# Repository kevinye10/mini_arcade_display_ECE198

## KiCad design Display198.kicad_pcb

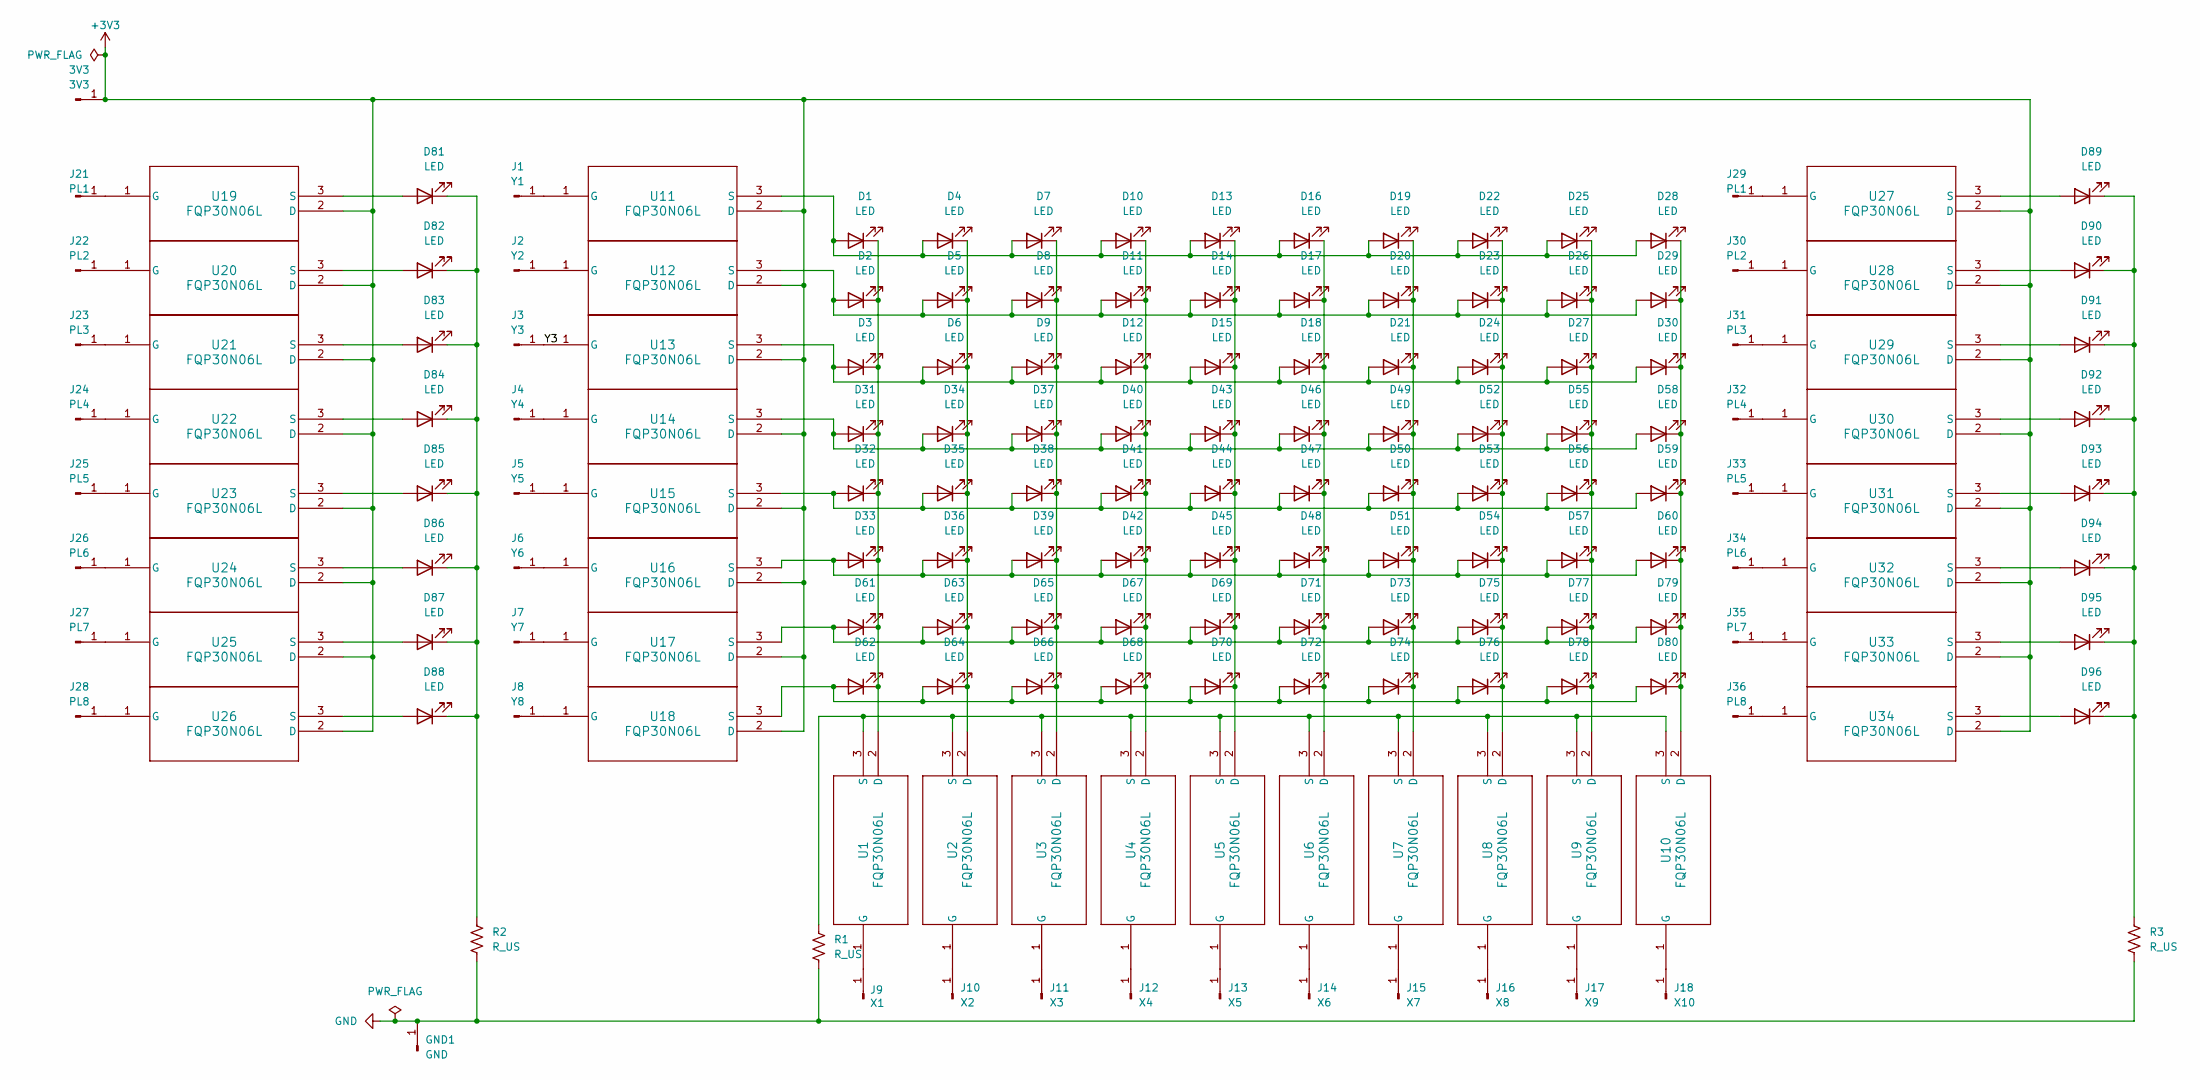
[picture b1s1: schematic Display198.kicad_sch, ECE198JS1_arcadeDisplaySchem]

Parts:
3V3: 3V3; Pin_D1.0mm_L10.0mm
D1, D2, D3, D4, D5, D6, D7, D8, D9, D10, D11, D12, D13, D14, D15, D16, D17, D18, D19, D20, D21, D22, D23, D24, D25, D26, D27, D28, D29, D30, D31, D32, D33, D34, D35, D36, D37, D38, D39, D40, D41, D42, D43, D44, D45, D46, D47, D48, D49, D50, D51, D52, D53, D54, D55, D56, D57, D58, D59, D60, D61, D62, D63, D64, D65, D66, D67, D68, D69, D70, D71, D72, D73, D74, D75, D76, D77, D78, D79, D80, D81, D82, D83, D84, D85, D86, D87, D88, D89, D90, D91, D92, D93, D94, D95, D96: LED; D_5W_P5.08mm_Vertical_AnodeUp
GND1: GND; Pin_D1.0mm_L10.0mm
J1: Y1; Pin_D1.0mm_L10.0mm
J2: Y2; Pin_D1.0mm_L10.0mm
J3: Y3; Pin_D1.0mm_L10.0mm
J4: Y4; Pin_D1.0mm_L10.0mm
J5: Y5; Pin_D1.0mm_L10.0mm
J6: Y6; Pin_D1.0mm_L10.0mm
J7: Y7; Pin_D1.0mm_L10.0mm
J8: Y8; Pin_D1.0mm_L10.0mm
J9: X1; Pin_D1.0mm_L10.0mm
J10: X2; Pin_D1.0mm_L10.0mm
J11: X3; Pin_D1.0mm_L10.0mm
J12: X4; Pin_D1.0mm_L10.0mm
J13: X5; Pin_D1.0mm_L10.0mm
J14: X6; Pin_D1.0mm_L10.0mm
J15: X7; Pin_D1.0mm_L10.0mm
J16: X8; Pin_D1.0mm_L10.0mm
J17: X9; Pin_D1.0mm_L10.0mm
J18: X10; Pin_D1.0mm_L10.0mm
J21, J29: PL1; Pin_D1.0mm_L10.0mm
J22, J30: PL2; Pin_D1.0mm_L10.0mm
J23, J31: PL3; Pin_D1.0mm_L10.0mm
J24, J32: PL4; Pin_D1.0mm_L10.0mm
J25, J33: PL5; Pin_D1.0mm_L10.0mm
J26, J34: PL6; Pin_D1.0mm_L10.0mm
J27, J35: PL7; Pin_D1.0mm_L10.0mm
J28, J36: PL8; Pin_D1.0mm_L10.0mm
R1, R2, R3: R_US; R_Axial_DIN0411_L9.9mm_D3.6mm_P7.62mm_Vertical
U1, U2, U3, U4, U5, U6, U7, U8, U9, U10, U11, U12, U13, U14, U15, U16, U17, U18, U19, U20, U21, U22, U23, U24, U25, U26, U27, U28, U29, U30, U31, U32, U33, U34: FQP30N06L; TO220-3_ONS

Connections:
+3V3: 3V3.1, U11.2 (D), U12.2 (D), U13.2 (D), U14.2 (D), U15.2 (D), U16.2 (D), U17.2 (D), U18.2 (D), U19.2 (D), U20.2 (D), U21.2 (D), U22.2 (D), U23.2 (D), U24.2 (D), U25.2 (D), U26.2 (D), U27.2 (D), U28.2 (D), U29.2 (D), U30.2 (D), U31.2 (D), U32.2 (D), U33.2 (D), U34.2 (D)
/Y3: J3.1, U13.1 (G)
GND: GND1.1, R1.1, R2.1, R3.1
unnamed: D1.2 (A), D4.2 (A), D7.2 (A), D10.2 (A), D13.2 (A), D16.2 (A), D19.2 (A), D22.2 (A), D25.2 (A), D28.2 (A), U11.3 (S)
unnamed: D1.1 (K), D2.1 (K), D3.1 (K), D31.1 (K), D32.1 (K), D33.1 (K), D61.1 (K), D62.1 (K), U1.2 (D)
unnamed: D10.1 (K), D11.1 (K), D12.1 (K), D40.1 (K), D41.1 (K), D42.1 (K), D67.1 (K), D68.1 (K), U4.2 (D)
unnamed: D2.2 (A), D5.2 (A), D8.2 (A), D11.2 (A), D14.2 (A), D17.2 (A), D20.2 (A), D23.2 (A), D26.2 (A), D29.2 (A), U12.3 (S)
unnamed: D3.2 (A), D6.2 (A), D9.2 (A), D12.2 (A), D15.2 (A), D18.2 (A), D21.2 (A), D24.2 (A), D27.2 (A), D30.2 (A), U13.3 (S)
unnamed: D13.1 (K), D14.1 (K), D15.1 (K), D43.1 (K), D44.1 (K), D45.1 (K), D69.1 (K), D70.1 (K), U5.2 (D)
unnamed: D16.1 (K), D17.1 (K), D18.1 (K), D46.1 (K), D47.1 (K), D48.1 (K), D71.1 (K), D72.1 (K), U6.2 (D)
unnamed: D19.1 (K), D20.1 (K), D21.1 (K), D49.1 (K), D50.1 (K), D51.1 (K), D73.1 (K), D74.1 (K), U7.2 (D)
unnamed: D22.1 (K), D23.1 (K), D24.1 (K), D52.1 (K), D53.1 (K), D54.1 (K), D75.1 (K), D76.1 (K), U8.2 (D)
unnamed: D25.1 (K), D26.1 (K), D27.1 (K), D55.1 (K), D56.1 (K), D57.1 (K), D77.1 (K), D78.1 (K), U9.2 (D)
unnamed: D28.1 (K), D29.1 (K), D30.1 (K), D58.1 (K), D59.1 (K), D60.1 (K), D79.1 (K), D80.1 (K), U10.2 (D)
unnamed: D31.2 (A), D34.2 (A), D37.2 (A), D40.2 (A), D43.2 (A), D46.2 (A), D49.2 (A), D52.2 (A), D55.2 (A), D58.2 (A), U14.3 (S)
unnamed: D32.2 (A), D35.2 (A), D38.2 (A), D41.2 (A), D44.2 (A), D47.2 (A), D50.2 (A), D53.2 (A), D56.2 (A), D59.2 (A), U15.3 (S)
unnamed: D33.2 (A), D36.2 (A), D39.2 (A), D42.2 (A), D45.2 (A), D48.2 (A), D51.2 (A), D54.2 (A), D57.2 (A), D60.2 (A), U16.3 (S)
unnamed: D4.1 (K), D5.1 (K), D6.1 (K), D34.1 (K), D35.1 (K), D36.1 (K), D63.1 (K), D64.1 (K), U2.2 (D)
unnamed: D7.1 (K), D8.1 (K), D9.1 (K), D37.1 (K), D38.1 (K), D39.1 (K), D65.1 (K), D66.1 (K), U3.2 (D)
unnamed: D61.2 (A), D63.2 (A), D65.2 (A), D67.2 (A), D69.2 (A), D71.2 (A), D73.2 (A), D75.2 (A), D77.2 (A), D79.2 (A), U17.3 (S)
unnamed: D62.2 (A), D64.2 (A), D66.2 (A), D68.2 (A), D70.2 (A), D72.2 (A), D74.2 (A), D76.2 (A), D78.2 (A), D80.2 (A), U18.3 (S)
unnamed: D81.2 (A), U19.3 (S)
unnamed: D81.1 (K), D82.1 (K), D83.1 (K), D84.1 (K), D85.1 (K), D86.1 (K), D87.1 (K), D88.1 (K), R2.2
unnamed: D82.2 (A), U20.3 (S)
unnamed: D83.2 (A), U21.3 (S)
unnamed: D84.2 (A), U22.3 (S)
unnamed: D85.2 (A), U23.3 (S)
unnamed: D86.2 (A), U24.3 (S)
unnamed: D87.2 (A), U25.3 (S)
unnamed: D88.2 (A), U26.3 (S)
unnamed: D89.2 (A), U27.3 (S)
unnamed: D89.1 (K), D90.1 (K), D91.1 (K), D92.1 (K), D93.1 (K), D94.1 (K), D95.1 (K), D96.1 (K), R3.2
unnamed: D90.2 (A), U28.3 (S)
unnamed: D91.2 (A), U29.3 (S)
unnamed: D92.2 (A), U30.3 (S)
unnamed: D93.2 (A), U31.3 (S)
unnamed: D94.2 (A), U32.3 (S)
unnamed: D95.2 (A), U33.3 (S)
unnamed: D96.2 (A), U34.3 (S)
unnamed: J1.1, U11.1 (G)
unnamed: J2.1, U12.1 (G)
unnamed: J4.1, U14.1 (G)
unnamed: J5.1, U15.1 (G)
unnamed: J6.1, U16.1 (G)
unnamed: J7.1, U17.1 (G)
unnamed: J8.1, U18.1 (G)
unnamed: J9.1, U1.1 (G)
unnamed: J10.1, U2.1 (G)
unnamed: J11.1, U3.1 (G)
unnamed: J12.1, U4.1 (G)
unnamed: J13.1, U5.1 (G)
unnamed: J14.1, U6.1 (G)
unnamed: J15.1, U7.1 (G)
unnamed: J16.1, U8.1 (G)
unnamed: J17.1, U9.1 (G)
unnamed: J18.1, U10.1 (G)
unnamed: J21.1, U19.1 (G)
unnamed: J22.1, U20.1 (G)
unnamed: J23.1, U21.1 (G)
unnamed: J24.1, U22.1 (G)
unnamed: J25.1, U23.1 (G)
unnamed: J26.1, U24.1 (G)
unnamed: J27.1, U25.1 (G)
unnamed: J28.1, U26.1 (G)
unnamed: J29.1, U27.1 (G)
unnamed: J30.1, U28.1 (G)
unnamed: J31.1, U29.1 (G)
unnamed: J32.1, U30.1 (G)
unnamed: J33.1, U31.1 (G)
unnamed: J34.1, U32.1 (G)
unnamed: J35.1, U33.1 (G)
unnamed: J36.1, U34.1 (G)
unnamed: R1.2, U1.3 (S), U2.3 (S), U3.3 (S), U4.3 (S), U5.3 (S), U6.3 (S), U7.3 (S), U8.3 (S), U9.3 (S), U10.3 (S)

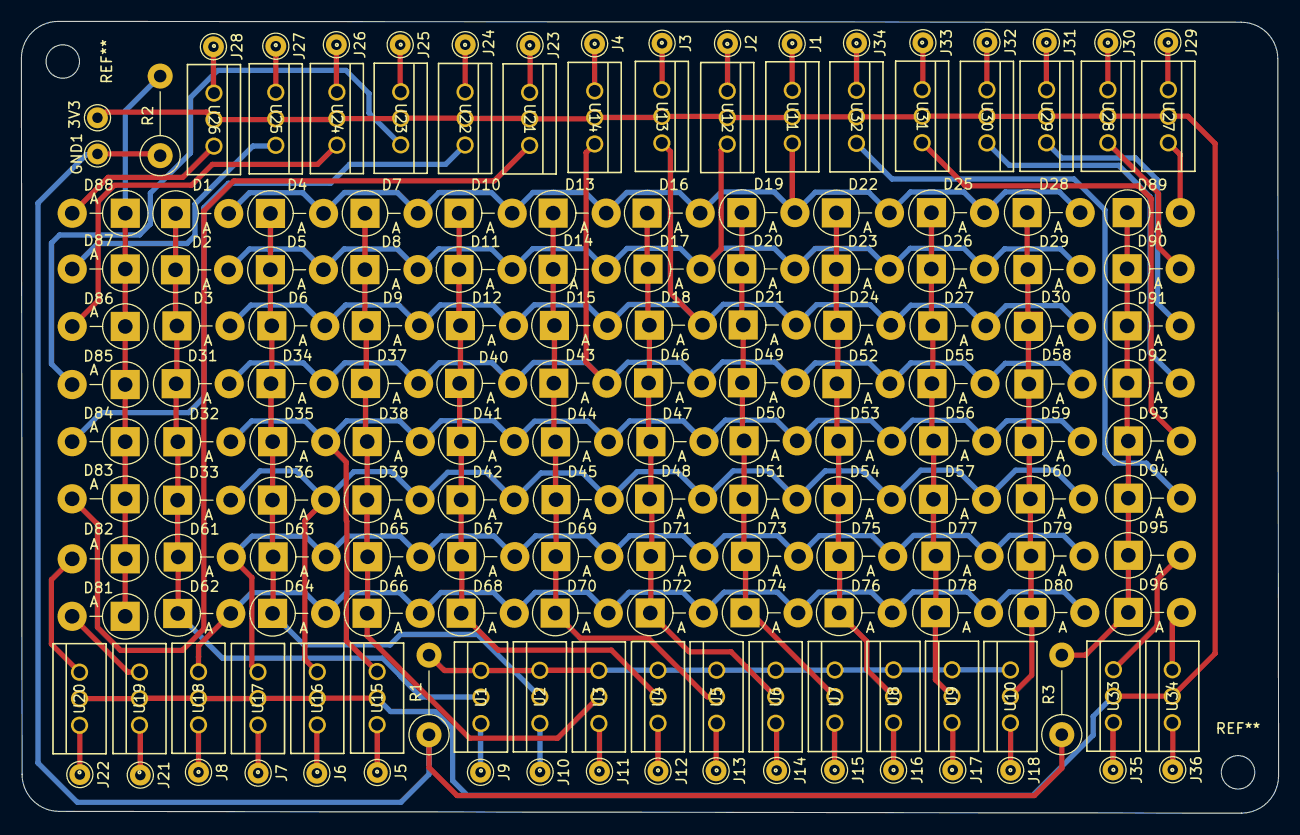
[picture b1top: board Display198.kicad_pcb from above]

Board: 2 copper layers, 120.4 x 75.8 mm, 169 parts (0 on the bottom side), 73 nets.

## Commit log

2023-11-02 first PCB draft
2023-11-02 removed backups from repo
2023-11-03 changed all track widths to 20mils
